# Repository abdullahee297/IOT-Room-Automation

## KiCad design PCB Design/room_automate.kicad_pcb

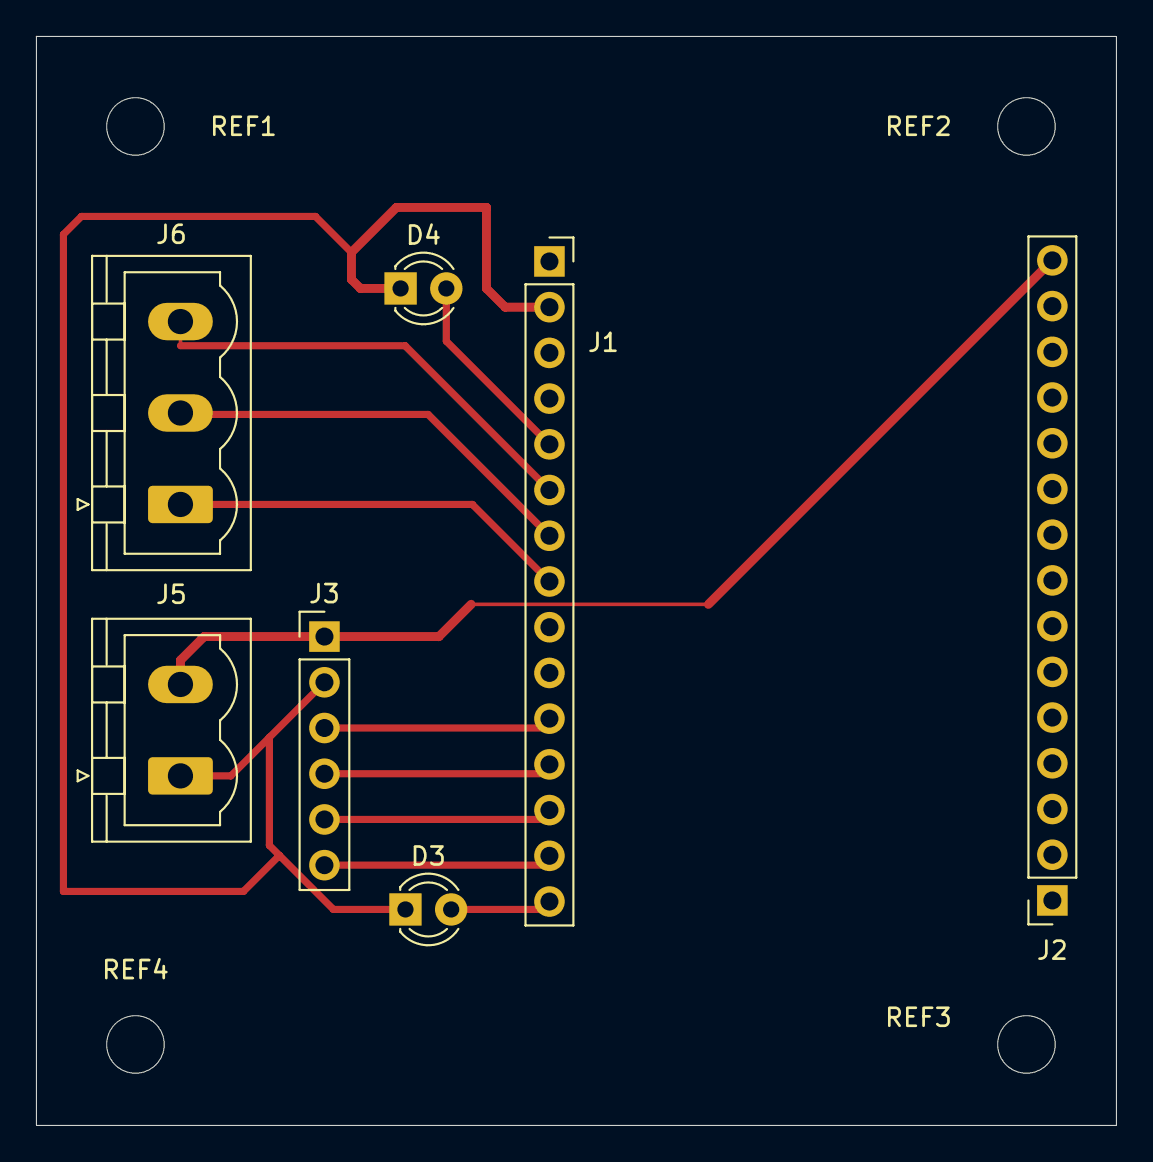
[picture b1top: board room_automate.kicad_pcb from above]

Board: 2 copper layers, 60.0 x 60.5 mm, 11 parts (0 on the bottom side), 11 nets.

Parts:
D3: RED LED; LED_D3.0mm
D4: GREEN LED; LED_D3.0mm
J1, J2: PinSocket_1x15_P2.54mm_Vertical
J3: RELAY PINS; PinHeader_1x06_P2.54mm_Vertical
J5: con 2; PhoenixContact_MSTBVA_2,5_2-G-5,08_1x02_P5.08mm_Vertical
J6: con 3; PhoenixContact_MSTBVA_2,5_3-G-5,08_1x03_P5.08mm_Vertical
REF1: 1; MountingHole_3.2mm_M3
REF2: 2; MountingHole_3.2mm_M3
REF3: 3; MountingHole_3.2mm_M3
REF4: 4; MountingHole_3.2mm_M3

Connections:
GND: D3.1 (K), D4.1 (K), J1.2, J3.2, J5.1
unnamed: D3.2 (A), J1.15
unnamed: D4.2 (A), J1.5
unnamed: J1.6, J6.3
unnamed: J1.7, J6.2
unnamed: J1.8, J6.1
unnamed: J1.11, J3.3
unnamed: J1.12, J3.4
unnamed: J1.13, J3.5
unnamed: J1.14, J3.6
unnamed: J2.15, J3.1, J5.2

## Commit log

2026-05-31 PCB Circuit
